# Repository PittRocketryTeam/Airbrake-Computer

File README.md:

# Airbrake-Computer
Code for the dedicated airbrake computer on the vehicle

LaunchVehicle methods: 
    (a) Descent detection: This method will primarily look at the altimeter data and its altitude readings. 
        (i) Global variables:
            1.  long highest_alt ---> Keeps track of the highest recorded altitude
            2.  bool hasMax ----> A flag that indicates that highest_alt has been initialized
            3.  int isConsistent ---> A counter that will increment each time a descent has been detected
        (ii) Implementation:
            In each iteration, the method will poll the altitmeter's altitude data. The data will be compared
            to the highest_alt global variable. If the altitude data in that method call is less than the 
            highest_alt global variable, this will assume that the rocket has made a descent. To verify that 
            the launch vehicle has descended, the isConsistent global variable will be incremented by one. 
            The counter will have a certain threshold, a max value. Once the threshold has been reached, 
            the method will finally return true to state that the descent has been detected.

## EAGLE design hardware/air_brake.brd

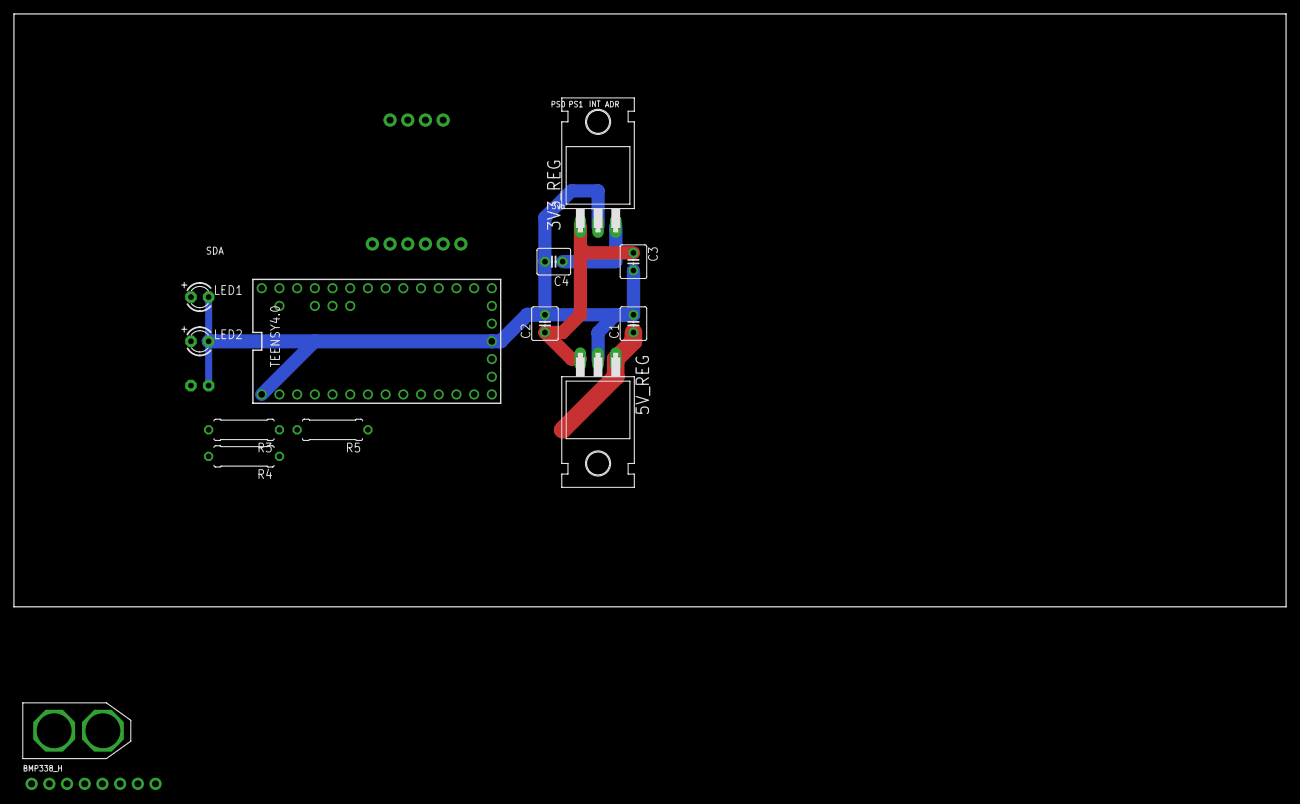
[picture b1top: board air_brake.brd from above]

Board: 2 copper layers, 182.6 x 85.1 mm, 17 parts (1 on the bottom side), 13 nets.

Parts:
3V3_REG, 5V_REG: 7812T; TO220H
BMP338_H: 1X08_ROUND_70
C1, C2, C3, C4: 22uF; C025-040X050
JP4: 1X06_ROUND_76
JP5: 1X04_ROUND_76
LED1, LED2, LED3: LED3MM
R3, R4, R5: 1k; 0309/10
TEENSY4.0: TEENSY_3.0_ALL_PINS; TEENSY_3.0-3.2&LC_ALL_PINS
U$1: XT60

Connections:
3.3V: TEENSY4.0.3.3V, TEENSY4.0.3.3V1
+3V3: 3V3_REG.3, BMP338_H.1, C4.1, TEENSY4.0.VIN
+5V: 3V3_REG.1, 5V_REG.3, C2.1, C3.1, JP4.1
GND: 3V3_REG.2, 5V_REG.2, BMP338_H.3, C1.2, C2.2, C3.2, C4.2, JP4.3, JP5.4, LED1.K, LED2.K, LED3.K, TEENSY4.0.AGND, TEENSY4.0.GND, TEENSY4.0.GND1, U$1.-
LED_1: R3.1, TEENSY4.0.0
LED_2: R4.1, TEENSY4.0.1
LED_3: R5.1, TEENSY4.0.2
unnamed: LED1.A, R3.2
unnamed: LED2.A, R4.2
unnamed: LED3.A, R5.2
SCL: BMP338_H.4, JP4.5, TEENSY4.0.19/A5
SDA: BMP338_H.6, JP4.4, TEENSY4.0.18/A4
V_BATT: 5V_REG.1, C1.1, U$1.+

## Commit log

2019-09-23 first shecmatic commit
2019-09-23 added unwanted eagle file extensions
2019-09-23 removed backup files
2019-09-23 updated cap values
2019-09-25 very rough prelim board layout
2019-10-03 began power routing
2019-11-29 updated to reflect no logging
2019-12-02 Changes to Airbrake Sch.
    Add 5V and Motor
2019-12-03 Added 5V Reg and stepper motor
2019-12-19 Created outline of airbrake software implementation
2019-12-19 Added IMU and altimeter code
2019-12-20 Created mock IMU class for testing
2019-12-20 Fixed mock sensor classes to read data from SD card
2019-12-20 Added failing unit tests for Airbrake class
2019-12-23 Added MockHelper and linter files
2019-12-28 Fixing mocked classes. added overarching abstract IMU and altimeter classes to make LaunchVehicle accept either mocked sensor classes or non-mocked sensor classes
2019-12-28 Now runs with MockHelper object; still need to figure out cause of serial monitor stalls (seems to be related to MockHelper)
2020-01-07 Changed to Teensy 3.6
2020-01-07 Added Buzzer
2020-01-08 add metro library
2020-01-12 add stepper library
2020-01-12 MockHelper micro SD reading is kinda working
2020-01-12 stupid pio files
2020-01-16 fixing stepper library
2020-01-16 stepper library is fixed
2020-01-29 Rearranged functions and added comments
2020-01-30 Small changes to sensor classes, closer to getting mockhelper working
2020-01-30 Moved verbose flag from board to constants
2020-01-30 Finished preliminary mockhelper class -- will need additional support to house more than 1500 data points
2020-01-31 uploaded datasets for testing
2020-02-01 added comments
2020-02-01 Added build flags and updated gitignore
2020-02-02 Added FLIGHT_BUILD flag
2020-02-02 Added altimeter calibration offset to mock sensor and real sensor readings
2020-02-02 Added stepper driver init
2020-02-05 Added preliminary implementation of predictApogee()
2020-02-05 Added descent detection implementation and updated README.md
2020-02-06 Added comments laying out the task and providing clarity
2020-02-06 Added function to detect if it's on the pad. Implemented the launch detect algorithm
2020-02-06 Added more conditions for launch and margin of error
2020-02-06 Added detection print statements
2020-02-06 Changed units to metric from imperial
2020-02-06 Changed FLIGHT_BUILD units to metric too
2020-02-06 updated gitignore
2020-02-08 Added teensy time lib
2020-02-09 updated readFromSensors()
2020-02-09 Changed all usages of poll() to readFromSensors()
2020-02-09 Added extra print statement to check data_index
2020-02-09 Fixed loop hogging the switch statment in the main sswitch statement. Changed control flow to if statements
2020-02-09 fixed readFromSensors()
2020-02-09 Added more comments and print statements for readibility. Fixed return statements.
2020-02-09 Changed from y to x axis
2020-02-09 Fixed some breaking changes
2020-02-09 Put variable declarations in the header
2020-02-09 added motor stuff
2020-02-09 comments from code review
2020-02-10 Fixed findGlobalMax to use ax^2 instead of cx^2
2020-02-11 filled in airbrake setAbsoluteDeployment() function based on preliminary testing with airbrake testbed
2020-02-11 Moved altimeter/imu creation and initialization from main to LaunchVehicle
2020-02-11 Copied over logging/timer tools from SCA
2020-02-14 Updated logger interface
